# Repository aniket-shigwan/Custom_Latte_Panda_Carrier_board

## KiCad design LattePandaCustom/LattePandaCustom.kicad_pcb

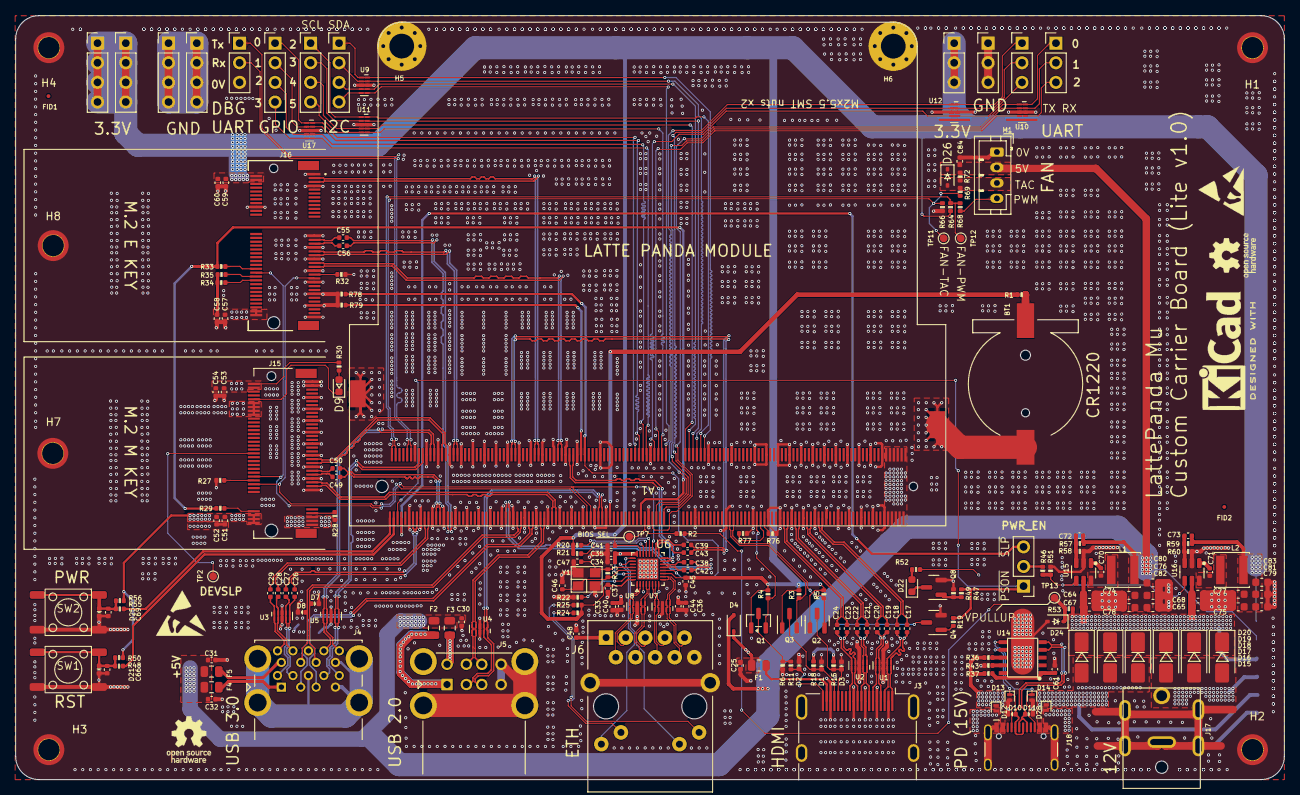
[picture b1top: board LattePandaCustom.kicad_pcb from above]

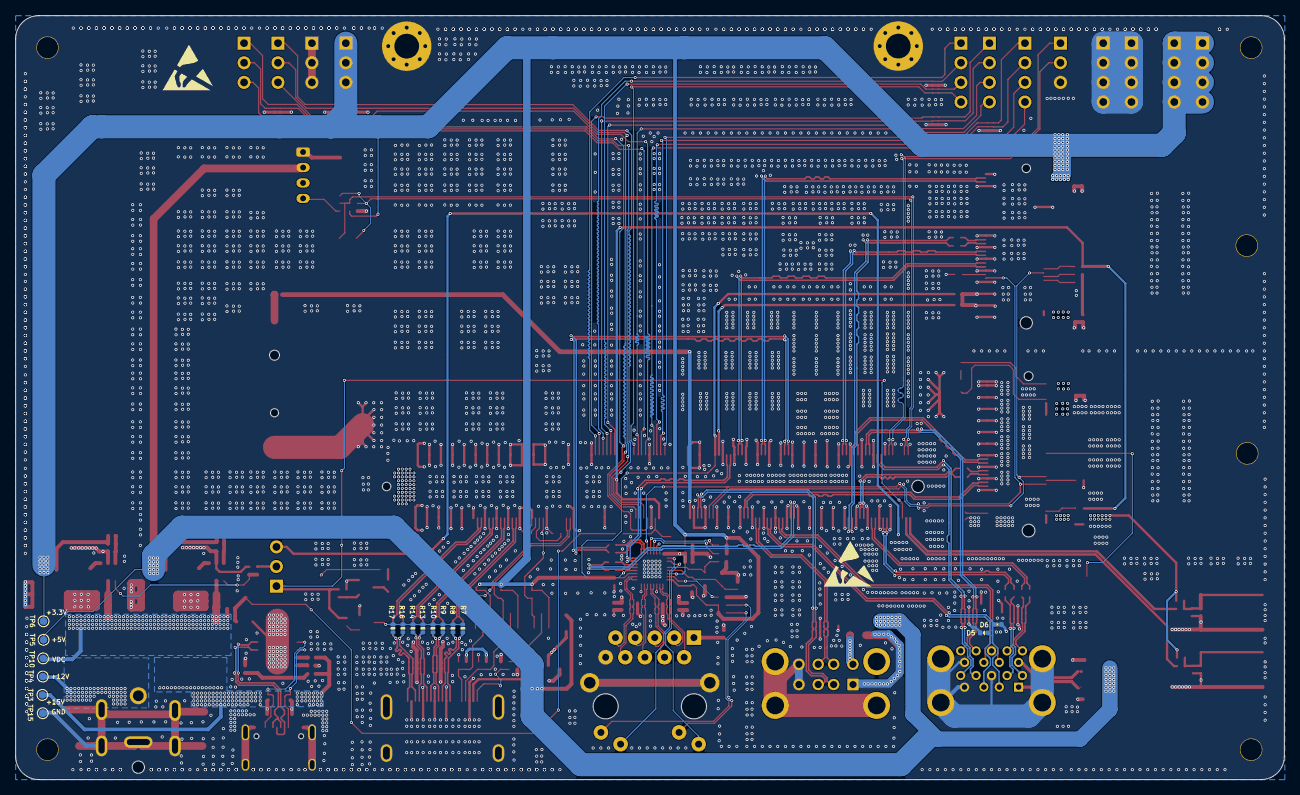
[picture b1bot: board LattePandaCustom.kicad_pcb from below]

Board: 4 copper layers, 164.2 x 98.9 mm, 226 parts (16 on the bottom side), 175 nets.

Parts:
A1: LattePanda_Mu; LattePanda_Module_H8.0mm_Horizontal
BT1: Battery_Cell; Battery_Holder_CR1220_S8411-45R
C17, C18, C19, C20, C21, C22, C23, C24, C25, C26, C27, C28, C29, C70, C71, C84: 100nF/50V; C_0402_1005Metric
C30, C31, C32: 22uF/10V; C_0402_1005Metric
C33, C34, C35, C36, C37, C38, C39, C40, C41, C42, C43, C45, C48: 100nF/16V; C_0402_1005Metric
C44: 10uF/16V; C_0402_1005Metric
C46, C47, C72, C73: 12pF/50V; C_0402_1005Metric
C49, C50, C55, C56: 220nF/50V; C_0402_1005Metric
C51, C53, C57, C59: 10uF/10V; C_0402_1005Metric
C52, C54, C58, C60: 100nF/10V; C_0402_1005Metric
C61, C66, C69: 1uf/16V; C_0402_1005Metric
C64, C65, C67, C68, C74, C75, C76, C77, C78, C79, C80, C81, C82, C83: 22uF/10V; C_0603_1608Metric
D1, D2, D3, D5, D6, D7, D8, D10, D11, D21, D25: ESD5V0B03-1006; D_0402_1005Metric
D4, D26: 1N5819WS; D_SOD-323
D9, D22: LED_G; LED_0603_1608Metric
D12, D13, D14, D28: PESD3V3S1UL; D_SOD-882
D15, D16, D17, D18, D19, D20: SS54; D_SMA
D24: 3V3, Izt=5mA; D_SOD-323
F1: 6V/50mA; Fuse_0805_2012Metric
F2, F3: 6V/1A; Fuse_0805_2012Metric
F4, F5: 6V/2A; Fuse_0805_2012Metric
FID1, FID2: Fiducial; Fiducial_0.5mm_Mask1mm
H1, H2, H3, H4: MountingHole_Pad; MountingHole_2.7mm_M2_Pad_TopOnly
H5, H6: MountingHole_Pad; MountingHole_3.2mm_M3_Pad_Via
H7, H8: MountingHole_M2.0; MountingHole_2.7mm_M2_Pad_TopOnly
J1, J8, J10, J11, J14: Conn_01x03_Pin; PinHeader_1x03_P2.54mm_Vertical
J3: HDMI_A; HDMI_A_Molex_208658-1001_Horizontal
J4: USB3_A_Stacked; USB3_A_Molex_48406-0001_Horizontal_Stacked
J5: USB_A_Stacked; USB_A_CUI_UJ2-ADH-TH_Horizontal_Stacked
J6: RJ45_RB1-125B8G1A; RJ45_UDE_RB1-125B8G1A
J7, J9, J12, J13, J19, J20, J21: Conn_01x04_Pin; PinHeader_1x04_P2.54mm_Vertical
J15: Bus_M.2_Socket_M; PCIe_M.2_Connectors_P=0.5mm_H=4.2mm_KeyM
J16: Bus_M.2_Socket_E; PCIe_M.2_Connectors_P=0.5mm_H=4.2mm_KeyE
J17: Barrel_Jack_Switch; DC_Jack_DC007B_30V_10A
J18: USB_C_Receptacle_USB2.0_16P; USB_C_Receptacle_HCTL_HC-TYPE-C-16P-01A
JP1: Jumper_3_Bridged12; PinHeader_1x03_P2.54mm_Vertical
L1, L2: 2.2uH/4.3A; L_Sunlord_SWPA4020S
M1: Fan_4pin; JST_PH_B4B-PH-K_1x04_P2.00mm_Vertical
Q1, Q8: 2N7002; SOT-23
Q2, Q3, Q4: 2SK3018; SOT-23
R1, R37, R47: 1k / 1%; R_0402_1005Metric
R2, R36, R49, R50, R56, R78, R79: 10k / 1%; R_0402_1005Metric
R3, R5, R15, R18, R19, R30: 2.2K/1%; R_0402_1005Metric
R4, R23: 1M/1%; R_0402_1005Metric
R6: 21.5K/1%; R_0402_1005Metric
R7, R8, R9, R10, R13, R14, R16, R17, R24, R25: 470R/1%; R_0402_1005Metric
R11: 1K/1%; R_0402_1005Metric
R20, R21, R34, R35: 10K/1%; R_0402_1005Metric
R22: 2.49K/1%; R_0402_1005Metric
R27, R28, R29, R32, R33: 0R/1%; R_0402_1005Metric
R43: 56k / 1%; R_0402_1005Metric
R46, R51: 100k/1%; R_0402_1005Metric
R48: 100 R/ 1%; R_0402_1005Metric
R52: 2.2k / 1%; R_0402_1005Metric
R53: 2.2k/1%; R_0402_1005Metric
R55: 100R / 1%; R_0402_1005Metric
R57: 75k/1%; R_0402_1005Metric
R58: 10k/1%; R_0402_1005Metric
R59, R66, R68: 21.5k/1%; R_0402_1005Metric
R60, R64, R72: 4.7k/1%; R_0402_1005Metric
R69: 100R/1%; R_0402_1005Metric
R76, R77: 100k / 1%; R_0402_1005Metric
SW1, SW2: SW_Push; SW_Push_6x6x6
TP2, TP3, TP4, TP5, TP6, TP10, TP11, TP12, TP13, TP15: TestPoint; TestPoint_Pad_D1.0mm
TP7: BIOS_SEL; TestPoint_Pad_D1.0mm
U1, U2: TPAZ1O23-04F; Diodes_UDFN-10_1.0x2.5mm_P0.5mm
U3, U4, U5, U7, U8, U9, U10, U11, U12, U17: ULC0524; Diodes_UDFN-10_1.0x2.5mm_P0.5mm
U6: RTL8111H-CG-RH; QFN-32-1EP_4x4mm_P0.4mm_EP2.65x2.65mm
U14: USB PD等快充协议受电芯片-CH224K-ESSOP10; ESSOP-10-1EP_3.9x5mm_P1.0mm_EP3.2x2.3
U15, U16: LM2734X; TSOT-23-6
Y1: 25MHz; Crystal_SMD_3225-4Pin_3.2x2.5mm

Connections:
5V_HDMI_VCC: C25.2, D4.1 (K), F1.2, R15.1, R18.1
+1V0: C33.1, C34.1, C35.1, C36.1, C40.1, C44.1, U6.3 (AVDD10), U6.8 (AVDD10), U6.22 (DVDD10), U6.24 (REGOUT), U6.30 (AVDD10)
+3V3: C37.1, C41.1, C45.1, C51.1, C52.1, C53.1, C54.1, C57.1, C58.1, C59.1, C60.1, C73.2, C75.1, C77.1, C79.1, C81.1, C83.1, J13.1, J13.2, J13.3, J13.4, J14.1, J14.2, J14.3, J15.2 (3.3V), J15.4 (3.3V), J15.12 (3.3V), J15.14 (3.3V), J15.16 (3.3V), J15.18 (3.3V), J15.70 (3.3V), J15.72 (3.3V), J15.74 (3.3V), J16.2 (3.3V), J16.4 (3.3V), J16.72 (3.3V), J16.74 (3.3V), J21.1, J21.2, J21.3, J21.4, L2.2, Q1.1 (G), Q2.1 (G), Q3.1 (G), R3.1, R4.1, R5.1, R20.1, R21.1, R24.1, R25.1, R30.2, R34.2, R35.2, R50.2, R52.2, R56.2, R59.2, R64.2, TP6.1 (1_1), U6.11 (AVDD33), U6.23 (VDDREG), U6.32 (AVDD33)
+5V: C30.2, C31.2, C32.2, C72.2, C74.1, C76.1, C78.1, C80.1, C82.1, C84.1, D4.2 (A), D26.1 (K), F2.1, F3.1, F4.1, F5.1, L1.2, M1.2 (+), R57.2, R72.1, TP5.1 (1_1)
+12V: D15.2 (A), D16.2 (A), D17.2 (A), J17.1, TP4.1 (1_1)
+15V: D12.1 (K), D18.2 (A), D19.2 (A), D20.2 (A), D28.1 (K), J18.A4 (VBUS), J18.A9 (VBUS), J18.B4 (VBUS), J18.B9 (VBUS), R36.1, R37.1, TP3.1 (1_1)
+BATT: A1.115 (VBAT), R1.1
/FAN/FAN_1_PWM: A1.2 (FAN1_PWM), R64.1, R69.1, TP12.1 (1_1)
/FAN/FAN_1_TAC: A1.4 (FAN1_TAC), R66.2, R68.1, TP11.1 (1_1)
/GPIO/GPP_D0: A1.128 (GPP_D0), J19.1, U17.1, U17.10 (NC)
/GPIO/GPP_D1: A1.130 (GPP_D1), J19.2, U17.2, U17.9 (NC)
/GPIO/GPP_D2: A1.132 (GPP_D2), J19.3, U17.4, U17.7 (NC)
/GPIO/GPP_D3: A1.134 (GPP_D3), J19.4, U17.5, U17.6 (NC)
/GPIO/I2C2_SCL: A1.154 (I2C2_SCL), J9.1, U11.1, U11.10 (NC)
/GPIO/I2C2_SDA: A1.156 (I2C2_SDA), J7.1, U9.1, U9.10 (NC)
/GPIO/I2C3_SCL: A1.150 (I2C3_SCL), J9.2, U11.2, U11.9 (NC)
/GPIO/I2C3_SDA: A1.152 (I2C3_SDA), J7.2, U9.2, U9.9 (NC)
/GPIO/I2C4_SCL: A1.146 (I2C4_SCL), J9.3, U11.4, U11.7 (NC)
/GPIO/I2C4_SDA: A1.148 (I2C4_SDA), J7.3, U9.4, U9.7 (NC)
/GPIO/I2C5_SCL: A1.142 (I2C5_SCL), J9.4, U11.5, U11.6 (NC)
/GPIO/I2C5_SDA: A1.144 (I2C5_SDA), J7.4, U9.5, U9.6 (NC)
/GPIO/SOC_UART0_RX: A1.137 (UART0_RXD), J8.1, U10.1, U10.10 (NC)
/GPIO/SOC_UART0_TX: A1.139 (UART0_TXD), J10.1, U12.1, U12.10 (NC)
/GPIO/SOC_UART1_RX: A1.141 (UART1_RXD), J8.2, U10.2, U10.9 (NC)
/GPIO/SOC_UART1_TX: A1.143 (UART1_TXD), J10.2, U12.2, U12.9 (NC)
/GPIO/SOC_UART2_RX: A1.140 (UART2_RXD), J8.3, U10.4, U10.7 (NC)
/GPIO/SOC_UART2_TX: A1.138 (UART2_TXD), J10.3, U12.4, U12.7 (NC)
/Gigabit Ethernet/GbE_PCIe_CLK+: A1.94 (REFCLK4+), U6.15 (REFCLK_P)
/Gigabit Ethernet/GbE_PCIe_CLK-: A1.96 (REFCLK4-), U6.16 (REFCLK_N)
/Gigabit Ethernet/GbE_PCIe_RX+: A1.64 (HSIO6_RX+), C43.1
/Gigabit Ethernet/GbE_PCIe_RX-: A1.66 (HSIO6_RX-), C39.1
/Gigabit Ethernet/GbE_PCIe_TX+: A1.61 (HSIO6_TX+), C42.1
/Gigabit Ethernet/GbE_PCIe_TX-: A1.63 (HSIO6_TX-), C38.1
/Gigabit Ethernet/HSI+: C42.2, U6.13 (HSIP)
/Gigabit Ethernet/HSI-: C38.2, U6.14 (HSIN)
/Gigabit Ethernet/HSO+: C43.2, U6.17 (HSOP)
/Gigabit Ethernet/HSO-: C39.2, U6.18 (HSON)
/Gigabit Ethernet/LED1_1000: J6.L4, U6.26 (LED1)
/Gigabit Ethernet/LED2_ACT: J6.L2, U6.25 (LED2)
/Gigabit Ethernet/MDI0+: J6.R2 (TD1+), U6.1 (MDIP0), U8.5, U8.6 (NC)
/Gigabit Ethernet/MDI0-: J6.R3 (TD1-), U6.2 (MDIN0), U8.4, U8.7 (NC)
/Gigabit Ethernet/MDI1+: J6.R4 (TD2+), U6.4 (MDIP1), U8.2, U8.9 (NC)
/Gigabit Ethernet/MDI1-: J6.R5 (TD2-), U6.5 (MDIN1), U8.1, U8.10 (NC)
/Gigabit Ethernet/MDI2+: J6.R6 (TD3+), U6.6 (MDIP2), U7.5, U7.6 (NC)
/Gigabit Ethernet/MDI2-: J6.R7 (TD3-), U6.7 (MDIN2), U7.4, U7.7 (NC)
/Gigabit Ethernet/MDI3+: J6.R8 (TD4+), U6.9 (MDIP3), U7.2, U7.9 (NC)
/Gigabit Ethernet/MDI3-: J6.R9 (TD4-), U6.10 (MDIN3), U7.1, U7.10 (NC)
/Gigabit Ethernet/~CLKREQ4: A1.102 (~CLKREQ4), R78.2, U6.12 (CLKREQB)
/HDMI/DDC_SCL: D3.1, J3.15 (SCL), Q2.3 (D), R15.2
/HDMI/DDC_SDA: D1.1, J3.16 (SDA), Q3.3 (D), R18.2
/HDMI/DDI_B_DDC_SCL: A1.171 (DDIB_DDC_SCL), Q2.2 (S), R5.2
/HDMI/DDI_B_DDC_SDA: A1.169 (DDIB_DDC_SDA), Q3.2 (S), R3.2
/HDMI/DDI_B_HPD: A1.183 (DDIB_HPD), Q1.2 (S), R4.2
/HDMI/DDI_B_TX0+: A1.217 (DDIB_TX0+), C17.2
/HDMI/DDI_B_TX0-: A1.215 (DDIB_TX0-), C18.2
/HDMI/DDI_B_TX1+: A1.211 (DDIB_TX1+), C19.2
/HDMI/DDI_B_TX1-: A1.209 (DDIB_TX1-), C20.2
/HDMI/DDI_B_TX2+: A1.205 (DDIB_TX2+), C21.2
/HDMI/DDI_B_TX2-: A1.203 (DDIB_TX2-), C22.2
/HDMI/DDI_B_TX3+: A1.199 (DDIB_TX3+), C23.2
/HDMI/DDI_B_TX3-: A1.197 (DDIB_TX3-), C24.2
/HDMI/HPD: D2.1, J3.19 (HPD), R11.2
/HDMI/TMDS_CK+: C23.1, J3.10 (CK+), R8.1, U2.4, U2.7 (NC)
/HDMI/TMDS_CK-: C24.1, J3.12 (CK-), R7.1, U2.5, U2.6 (NC)
/HDMI/TMDS_D0+: C21.1, J3.7 (D0+), R10.1, U2.1, U2.10 (NC)
/HDMI/TMDS_D0-: C22.1, J3.9 (D0-), R9.1, U2.2, U2.9 (NC)
/HDMI/TMDS_D1+: C19.1, J3.4 (D1+), R14.1, U1.4, U1.7 (NC)
/HDMI/TMDS_D1-: C20.1, J3.6 (D1-), R13.1, U1.5, U1.6 (NC)
/HDMI/TMDS_D2+: C17.1, J3.1 (D2+), R17.1, U1.1, U1.10 (NC)
/HDMI/TMDS_D2-: C18.1, J3.3 (D2-), R16.1, U1.2, U1.9 (NC)
/Latte Panda Module/HSIO_0_TX+: A1.13 (HSIO0_TX+), C27.1
/Latte Panda Module/HSIO_0_TX-: A1.15 (HSIO0_TX-), C26.1
/Latte Panda Module/HSIO_1_TX+: A1.19 (HSIO1_TX+), C29.1
/Latte Panda Module/HSIO_1_TX-: A1.21 (HSIO1_TX-), C28.1
/Latte Panda Module/HSIO_2_RX+: A1.28 (HSIO2_RX+), J15.43 (PERp0/SATA-B-)
/Latte Panda Module/HSIO_2_RX-: A1.30 (HSIO2_RX-), J15.41 (PERn0/SATA-B+)
/Latte Panda Module/HSIO_2_TX+: A1.25 (HSIO2_TX+), C49.1
/Latte Panda Module/HSIO_2_TX-: A1.27 (HSIO2_TX-), C50.1
/Latte Panda Module/HSIO_3_RX+: A1.34 (HSIO3_RX+), J16.41 (PERp0)
/Latte Panda Module/HSIO_3_RX-: A1.36 (HSIO3_RX-), J16.43 (PERn0)
/Latte Panda Module/HSIO_3_TX+: A1.31 (HSIO3_TX+), C55.1
/Latte Panda Module/HSIO_3_TX-: A1.33 (HSIO3_TX-), C56.1
/Latte Panda Module/REFCLK0+: A1.85 (REFCLK0+), J15.55 (REFCLKp)
/Latte Panda Module/REFCLK0-: A1.87 (REFCLK0-), J15.53 (REFCLKn)
/Latte Panda Module/REFCLK3+: A1.88 (REFCLK3+), J16.47 (REFCLKp0)
/Latte Panda Module/REFCLK3-: A1.90 (REFCLK3-), J16.49 (REFCLKn0)
/Latte Panda Module/SLS_S3: A1.7 (SLS_S3), JP1.3 (B)
/Latte Panda Module/SUSCLK_WIFI: A1.131 (SUSCLK), R29.1, R33.1
/Latte Panda Module/USB_2_P7+: A1.76 (USB2_P7+), J16.3 (USB_D+)
/Latte Panda Module/USB_2_P7-: A1.78 (USB2_P7-), J16.5 (USB_D-)
/Latte Panda Module/~PWR_SW: A1.1 (~PWRBTN), R55.1
/Latte Panda Module/~RST_SW: A1.3 (~RSTBTN), R48.1
/M.2 E&M/CON_PCIE_TX_0+: C55.2, J16.35 (PETp0)
/M.2 E&M/CON_PCIE_TX_0-: C56.2, J16.37 (PETn0)
/M.2 E&M/CON_PCIE_TX_1+: C49.2, J15.49 (PETp0/SATA-A+)
/M.2 E&M/CON_PCIE_TX_1-: C50.2, J15.47 (PETn0/SATA-A-)
/M.2 E&M/~CLKREQE: J16.53 (~CLKREQ0), R32.1
/M.2 E&M/~CLKREQM: J15.52 (~CLKREQ), R27.1
/PSU/CC1: D13.1 (K), J18.A5 (CC1), U14.7 (CC1)
/PSU/CC2: D14.1 (K), J18.B5 (CC2), U14.6 (CC2)
/PSU/PWR_C_D+: D11.1, J18.A6 (D+), J18.B6 (D+), U14.4 (DP)
/PSU/PWR_C_D-: D10.1, J18.A7 (D-), J18.B7 (D-), U14.5 (DM)
/PSU/PWR_EN: R46.1, R51.2, U15.4 (EN), U16.4 (EN)
/USB 2.0 and 3.0/CON_USB1_D_N: A1.109 (USB2_P5-), J5.2 (D1-), U4.2, U4.9 (NC)
/USB 2.0 and 3.0/CON_USB1_D_P: A1.111 (USB2_P5+), J5.3 (D1+), U4.1, U4.10 (NC)
/USB 2.0 and 3.0/CON_USB2_D_N: A1.79 (USB2_P3-), J5.6 (D2-), U4.5, U4.6 (NC)
/USB 2.0 and 3.0/CON_USB2_D_P: A1.81 (USB2_P3+), J5.7 (D2+), U4.4, U4.7 (NC)
/USB 2.0 and 3.0/CON_USB3_D_N: A1.73 (USB2_P2-), D6.1, J4.2 (D1-)
/USB 2.0 and 3.0/CON_USB3_D_P: A1.75 (USB2_P2+), D5.1, J4.3 (D1+)
/USB 2.0 and 3.0/CON_USB3_SSRX_N: A1.18 (HSIO0_RX-), J4.5 (SSRX1-), U5.5, U5.6 (NC)
/USB 2.0 and 3.0/CON_USB3_SSRX_P: A1.16 (HSIO0_RX+), J4.6 (SSRX1+), U5.4, U5.7 (NC)
/USB 2.0 and 3.0/CON_USB3_SSTX_N: C26.2, J4.8 (SSTX1-), U3.5, U3.6 (NC)
/USB 2.0 and 3.0/CON_USB3_SSTX_P: C27.2, J4.9 (SSTX1+), U3.4, U3.7 (NC)
/USB 2.0 and 3.0/CON_USB4_D_N: A1.67 (USB2_P1-), D8.1, J4.11 (D2-)
/USB 2.0 and 3.0/CON_USB4_D_P: A1.69 (USB2_P1+), D7.1, J4.12 (D2+)
/USB 2.0 and 3.0/CON_USB4_SSRX_N: A1.24 (HSIO1_RX-), J4.14 (SSRX2-), U5.2, U5.9 (NC)
/USB 2.0 and 3.0/CON_USB4_SSRX_P: A1.22 (HSIO1_RX+), J4.15 (SSRX2+), U5.1, U5.10 (NC)
/USB 2.0 and 3.0/CON_USB4_SSTX_N: C28.2, J4.17 (SSTX2-), U3.2, U3.9 (NC)
/USB 2.0 and 3.0/CON_USB4_SSTX_P: C29.2, J4.18 (SSTX2+), U3.1, U3.10 (NC)
/~PLT_RST: A1.105 (~PLTRST), J15.50 (~PERST), J16.52 (~PERST0), U6.19 (PERSTB)
/~PWR_LED/~PSON: A1.5 (SLS_S0), JP1.1 (A), R19.1, R47.1
/~WAKE: A1.103 (~WAKE), J15.54 (~PEWAKE), J16.55 (~PEWAKE0)
GND: A1.11 (GND), A1.14 (GND), A1.17 (GND), A1.20 (GND), A1.23 (GND), A1.26 (GND), A1.29 (GND), A1.32 (GND), A1.35 (GND), A1.38 (GND), A1.41 (GND), A1.44 (GND), A1.47 (GND), A1.50 (GND), A1.53 (GND), A1.56 (GND), A1.59 (GND), A1.62 (GND), A1.65 (GND), A1.68 (GND), A1.71 (GND), A1.74 (GND), A1.77 (GND), A1.80 (GND), A1.83 (GND), A1.86 (GND), A1.89 (GND), A1.92 (GND), A1.95 (GND), A1.98 (GND), A1.101 (GND), A1.107 (GND), A1.110 (GND), A1.113 (GND), A1.116 (GND), A1.135 (GND), A1.136 (GND), A1.151 (GND), A1.158 (GND), A1.167 (GND), A1.170 (GND), A1.181 (GND), A1.182 (GND), A1.188 (GND), A1.189 (GND), A1.194 (GND), A1.195 (GND), A1.200 (GND), A1.201 (GND), A1.206 (GND), A1.207 (GND), A1.212 (GND), A1.213 (GND), A1.218 (GND), A1.219 (GND), A1.224 (GND), A1.225 (GND), A1.230 (GND), A1.231 (GND), A1.236 (GND), A1.237 (GND), A1.242 (GND), A1.243 (GND), A1.248 (GND), A1.249 (GND), A1.MP (Mountinge_Pads), BT1.2 (-), C25.1, C30.1, C31.1, C32.1, C33.2, C34.2, C35.2, C36.2, C37.2, C40.2, C41.2, C44.2, C45.2, C46.2, C47.1, C48.2, C51.2, C52.2, C53.2, C54.2, C57.2, C58.2, C59.2, C60.2, C61.1, C64.2, C65.1, C66.1, C67.2, C68.1, C69.1, C74.2, C75.2, C76.2, C77.2, C78.2, C79.2, C80.2, C81.2, C82.2, C83.2, C84.2, D1.2, D2.2, D3.2, D5.2, D6.2, D7.2, D8.2, D10.2, D11.2, D12.2 (A), D13.2 (A), D14.2 (A), D21.2, D24.2 (A), D25.2, D28.2 (A), H1.1 (1_1), H2.1 (1_1), H3.1 (1_1), H4.1 (1_1), H5.1 (1_1), H6.1 (1_1), H7.1 (1_1), H8.1 (1_1), J1.3, J3.2 (D2S), J3.5 (D1S), J3.8 (D0S), J3.11 (CKS), J3.17 (GND), J3.SH, J4.4 (GND1), J4.7 (DRAIN1), J4.13 (GND2), J4.16 (DRAIN2), J5.4 (GND1), J5.8 (GND2), J6.R10 (GND), J6.SH, J11.1, J11.2, J11.3, J12.1, J12.2, J12.3, J12.4, J15.1 (GND), J15.3 (GND), J15.9 (GND), J15.15 (GND), J15.21 (GND), J15.27 (GND), J15.33 (GND), J15.39 (GND), J15.45 (GND), J15.51 (GND), J15.57 (GND), J15.71 (GND), J15.73 (GND), J15.75 (GND), J16.1 (GND), J16.7 (GND), J16.18 (GND), J16.33 (GND), J16.39 (GND), J16.45 (GND), J16.51 (GND), J16.57 (GND), J16.63 (GND), J16.69 (GND), J16.75 (GND), J17.2, J17.3, J18.A1 (GND), J18.A12 (GND), J18.B1 (GND), J18.B12 (GND), J18.SH (SHIELD), J20.1, J20.2, J20.3, J20.4, M1.1 (-), Q4.2 (S), Q8.2 (S), R6.1, R22.1, R27.2, R28.1, R32.2, R43.2, R49.1, R51.1, R58.1, R60.1, R66.1, R76.1, R77.1, R78.1, R79.1, SW1.2, SW2.2, TP15.1 (1_1), U1.3 (VSS), U1.8 (VSS), U2.3 (VSS), U2.8 (VSS), U3.3 (VSS), U3.8 (VSS), U4.3 (VSS), U4.8 (VSS), U5.3 (VSS), U5.8 (VSS), U6.33 (GND), U7.3 (VSS), U7.8 (VSS), U8.3 (VSS), U8.8 (VSS), U9.3 (VSS), U9.8 (VSS), U10.3 (VSS), U10.8 (VSS), U11.3 (VSS), U11.8 (VSS), U12.3 (VSS), U12.8 (VSS), U14.0 (GND), U15.2 (GND), U16.2 (GND), U17.3 (VSS), U17.8 (VSS), Y1.2 (G), Y1.4 (G)
unnamed: A1.12 (SIO_UART_RX), J1.2
unnamed: A1.10 (SIO_UART_TX), J1.1
unnamed: A1.187 (TCP0_HPD), R76.2
unnamed: A1.185 (TCP1_HPD), R77.2
unnamed: A1.133 (~BIOS_SEL), R2.1, TP7.1 (1_1)
unnamed: A1.100 (~CLKREQ3), R79.2
unnamed: BT1.1 (+), R1.2
unnamed: C66.2, D21.1, R48.2, R50.1, SW1.1
unnamed: C69.2, D25.1, R55.2, R56.1, SW2.1
unnamed: D9.2 (A), R30.1
unnamed: D9.1 (K), J15.10 (DAS/~DSS/~LED1)
unnamed: D22.2 (A), R52.1
unnamed: D22.1 (K), Q8.3 (D)
unnamed: D26.2 (A), M1.3 (Tacho), R68.2, R72.2
unnamed: F1.1, J3.18 (+5V)
unnamed: F4.2, J4.1 (VBUS1)
unnamed: F5.2, J4.10 (VBUS2)
unnamed: F2.2, J5.1 (VBUS1)
unnamed: F3.2, J5.5 (VBUS2)
unnamed: C48.1, J6.R1 (CT)
unnamed: J6.L1, R25.2
unnamed: J6.L3, R24.2
unnamed: J15.38 (DEVSLP), TP2.1 (1_1)
unnamed: J15.69 (PEDET), R28.2
unnamed: J15.68 (SUSCLK), R29.2
unnamed: J16.50 (SUSCLK), R33.2
unnamed: J16.56 (~W_DISABLE1), R34.1
unnamed: J16.54 (~W_DISABLE2), R35.1
unnamed: JP1.2 (C), R46.2
unnamed: M1.4 (PWM), R69.2
unnamed: Q1.3 (D), R6.2, R11.1
unnamed: Q4.3 (D), R7.2, R8.2, R9.2, R10.2, R13.2, R14.2, R16.2, R17.2
unnamed: Q4.1 (G), R19.2
unnamed: Q8.1 (G), R47.2, R49.2
unnamed: C47.2, R23.1, U6.28 (CKXTAL1), Y1.3
unnamed: C46.1, R23.2, U6.29 (CKXTAL2), Y1.1
unnamed: R20.2, U6.20 (ISOLATEB)
unnamed: R21.2, U6.21 (LANWAKEB)
unnamed: R22.2, U6.31 (RSET)
unnamed: U10.5, U10.6 (NC)
unnamed: U12.5, U12.6 (NC)
unnamed: R43.1, U14.9 (CFG1)
unnamed: R36.2, U14.8 (VBUS)
unnamed: C61.2, R37.2, U14.1 (VDD)
unnamed: C70.1, U15.1 (BOOST)
unnamed: C72.1, R57.1, R58.2, U15.3 (FB)
unnamed: C70.2, L1.1, U15.6 (SW)
unnamed: C71.1, U16.1 (BOOST)
unnamed: C73.1, R59.1, R60.2, U16.3 (FB)
unnamed: C71.2, L2.1, U16.6 (SW)
VDC: A1.250 (VIN), A1.251 (VIN), A1.252 (VIN), A1.253 (VIN), A1.254 (VIN), A1.255 (VIN), A1.256 (VIN), A1.257 (VIN), A1.258 (VIN), A1.259 (VIN), A1.260 (VIN), C64.1, C65.2, C67.1, C68.2, D15.1 (K), D16.1 (K), D17.1 (K), D18.1 (K), D19.1 (K), D20.1 (K), R53.1, TP10.1 (1_1), U15.5 (VIN), U16.5 (VIN)
VPullup: D24.1 (K), R2.2, R53.2, TP13.1 (1_1)

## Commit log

2026-05-27 upload kicad pcb design files
2026-05-27 upload 3D images of the PCB
2026-05-28 added GND stitching vias to PCB and added 3D renders and PCB images
2026-06-08 Add files via upload
    A pdf document giving an overview of the design
